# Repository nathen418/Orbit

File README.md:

# Orbit

# What happened here?
Old design files for an Arduino based clock I was building. Most stuff here is not mine, I was going to modify the files. Lost all of my work. This repo exists only so that I may return to the project at a later date. At the moment I have no energy or will to continue working on it as months of work has been lost. I got as far as fully working code and fully working hardware. I had the pcb's printed and soldered everything onto them. They worked perfectly. I still have all of the 8 revisions to the hardware. MONTHS of work gone, so 🤷‍♂️ I don't know what I am going to do. If I do return to the project, I will have to start from scratch, and will probably choose a Raspberry Pi Pico as the microcontroller, but I really have no idea.

Maybe in the future I will find a backup of the files and return to the project, however this seems unlikely.

Toodles.

## Questions?
- **Contact me on discord at nathen418#0002 or join my discord server at the link below**

## Modifications
- no issues will be resolved
- no pull requests wil be merged
- no comments on files will be answered.
- If you have a question, contact me through my discord

## Join my discord server:
https://dsc.gg/antaresnetwork

## License

- Im not a legal person so as long as I am credited in a somewhat obvious location, by my name or a link to this repository, I'm ok with it. If my name is not at the top of the file in a comment, it was not written by me and is only in this repo to serve as an example of something I was using for help. If my name does not appear on the file in a comment at the top, than it is not my code, it is class material.  If you have a problem with any of this, refer to my discord server and dm me.

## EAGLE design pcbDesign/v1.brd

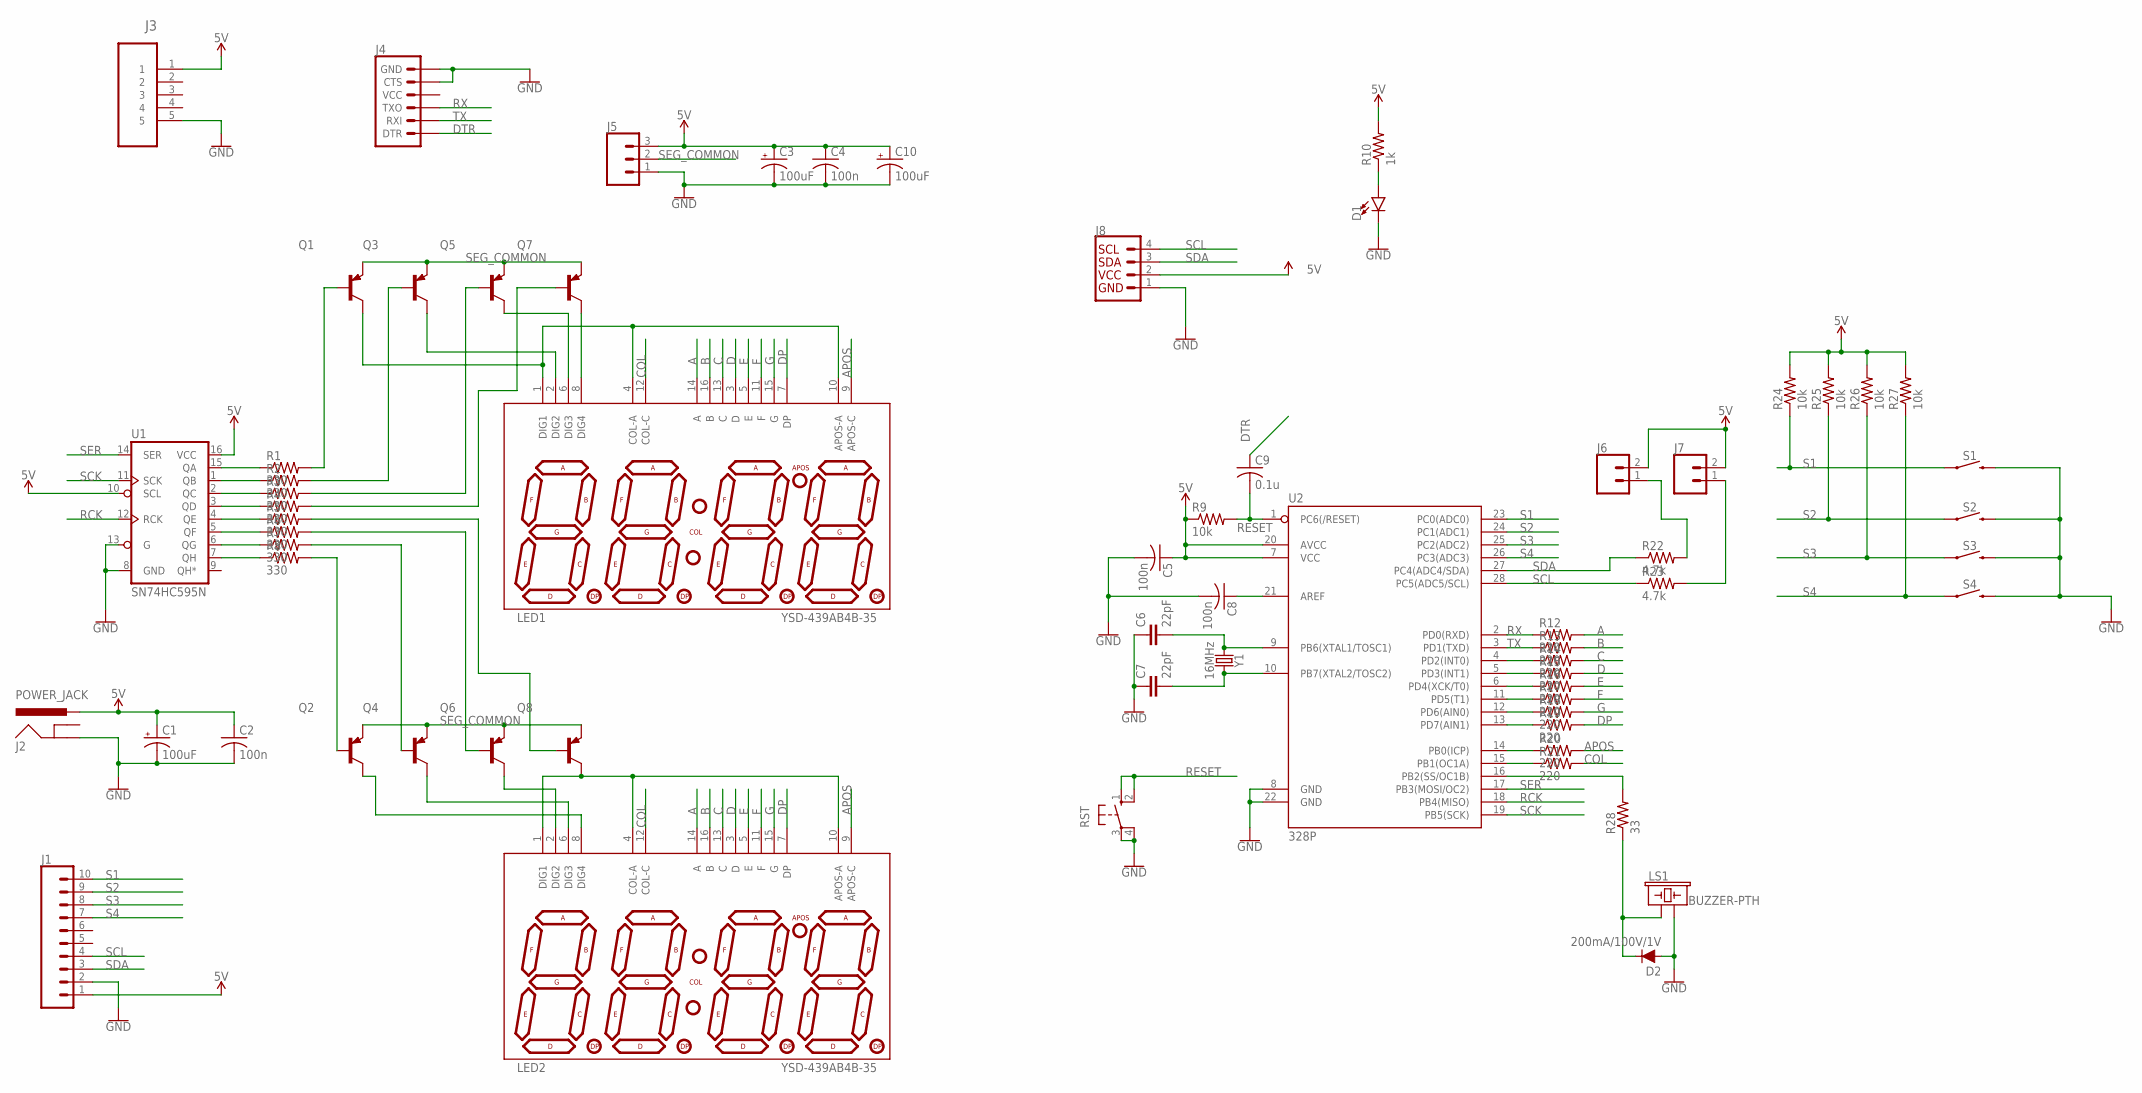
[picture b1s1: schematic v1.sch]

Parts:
C1, C3, C10: 100uF; CPOL-RADIAL-2.5MM-6.5MM
C2, C4, C5, C8: 100n; C025-025X050
C6, C7: 22pF; CAP-PTH-2.54
C9: 0.1u; C025-025X050
D1: LED3MM; LED_3MM
D2: 200mA/100V/1V; DIODE-1N4148
J1: CONN_10"; 1X10
J2: POWER_JACK; POWER_JACK_PTH
J3: 47346-0001; MOLEX_47346-0001
J4: 6_PIN_SERIAL_TARGET; 1X06
J5: CONN_03; 1X03
J6, J7: CONN_02; 1X02
J8: I2C_STANDARD; 1X04
LED1, LED2: YSD-439AB4B-35; 7-SEGMENT-4DIGIT-YOUNGSUN
LS1: BUZZER-PTH; BUZZER-12MM
Q1, Q2, Q3, Q4, Q5, Q6, Q7, Q8: 2N3906; TO92
R1, R2, R3, R4, R5, R6, R7, R8: 330; 0204/5
R9, R24, R25, R26, R27: 10k; 0204/5
R10: 1k; 0204/5
R12, R13, R14, R15, R16, R17, R18, R19, R20, R21: 220; 0204/5
R22, R23: 4.7k; 0204/5
R28: 33; 0204/5
RST: 10-XX; B3F-10XX
S1, S2, S3, S4: MOMENTARY-SWITCH-SPST-PTH-6.0MM; TACTILE_SWITCH_PTH_6.0MM
U1: SN74HC595N; DIP16
U2: 328P; DIP28
Y1: 16MHz; HC49US

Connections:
5V: C1.1 (+), C2.1, C3.1 (+), C4.1, C5.1, C10.1 (+), J1.1, J2.PWR, J3.1, J5.3, J6.2, J7.2, J8.2, R9.1, R10.2, R24.2, R25.2, R26.2, R27.2, U1.10 (SCL), U1.16 (VCC), U2.7 (VCC), U2.20 (AVCC)
A: LED1.14 (A), LED2.14 (A), R12.2
APOS: LED1.9 (APOS-C), LED2.9 (APOS-C), R20.2
B: LED1.16 (B), LED2.16 (B), R13.2
C: LED1.13 (C), LED2.13 (C), R14.2
COL: LED1.12 (COL-C), LED2.12 (COL-C), R21.2
D: LED1.3 (D), LED2.3 (D), R15.2
DP: LED1.7 (DP), LED2.7 (DP), R19.2
DTR: C9.1, J4.1 (DTR)
E: LED1.5 (E), LED2.5 (E), R16.2
F: LED1.11 (F), LED2.11 (F), R17.2
G: LED1.15 (G), LED2.15 (G), R18.2
GND: C1.2 (-), C2.2, C3.2 (-), C4.2, C5.2, C6.1, C7.1, C8.2, C10.2 (-), D1.K (C), D2.A, J1.2, J2.GND, J3.5, J4.5 (CTS), J4.6 (GND), J5.1, J8.1, LS1.- (2), RST.3, RST.4 (P1), S1.3 (2), S2.3 (2), S3.3 (2), S4.3 (2), U1.8 (GND), U1.13 (G), U2.8 (GND), U2.22 (GND)
unnamed: D1.A, R10.1
unnamed: R21.1, U2.15 (PB1(OC1A))
unnamed: R14.1, U2.4 (PD2(INT0))
unnamed: R15.1, U2.5 (PD3(INT1))
unnamed: R16.1, U2.6 (PD4(XCK/T0))
unnamed: R17.1, U2.11 (PD5(T1))
unnamed: R18.1, U2.12 (PD6(AIN0))
unnamed: R19.1, U2.13 (PD7(AIN1))
unnamed: C6.2, U2.9 (PB6(XTAL1/TOSC1)), Y1.1
unnamed: C7.2, U2.10 (PB7(XTAL2/TOSC2)), Y1.2
unnamed: LED1.1 (DIG1), LED1.4 (COL-A), LED1.10 (APOS-A), Q1.1 (C)
unnamed: LED1.6 (DIG3), Q5.1 (C)
unnamed: LED1.2 (DIG2), Q3.1 (C)
unnamed: R28.2, U2.16 (PB2(SS/OC1B))
unnamed: LED2.1 (DIG1), LED2.4 (COL-A), LED2.10 (APOS-A), Q8.1 (C)
unnamed: D2.C, LS1.+ (1), R28.1
unnamed: LED2.2 (DIG2), Q6.1 (C)
unnamed: LED2.6 (DIG3), Q4.1 (C)
unnamed: LED2.8 (DIG4), Q2.1 (C)
unnamed: LED1.8 (DIG4), Q7.1 (C)
unnamed: Q1.2 (B), R1.2
unnamed: Q3.2 (B), R2.2
unnamed: Q5.2 (B), R3.2
unnamed: Q7.2 (B), R4.2
unnamed: Q8.2 (B), R5.2
unnamed: Q6.2 (B), R6.2
unnamed: Q4.2 (B), R7.2
unnamed: Q2.2 (B), R8.2
unnamed: R1.1, U1.15 (QA)
unnamed: R2.1, U1.1 (QB)
unnamed: R3.1, U1.2 (QC)
unnamed: R4.1, U1.3 (QD)
unnamed: R5.1, U1.4 (QE)
unnamed: R6.1, U1.5 (QF)
unnamed: R7.1, U1.6 (QG)
unnamed: R8.1, U1.7 (QH)
unnamed: C8.1, U2.21 (AREF)
unnamed: J6.1, R22.2
unnamed: J7.1, R23.2
unnamed: R20.1, U2.14 (PB0(ICP))
RCK: U1.12 (RCK), U2.18 (PB4(MISO))
RESET: C9.2, R9.2, RST.1 (S), RST.2 (S1), U2.1 (PC6(/RESET))
RX: J4.3 (TXO), R12.1, U2.2 (PD0(RXD))
S1: J1.10, R24.1, S1.1, U2.23 (PC0(ADC0))
S2: J1.9, R25.1, S2.1, U2.24 (PC1(ADC1))
S3: J1.8, R26.1, S3.1, U2.25 (PC2(ADC2))
S4: J1.7, R27.1, S4.1, U2.26 (PC3(ADC3))
SCK: U1.11 (SCK), U2.19 (PB5(SCK))
SCL: J1.4, J8.4, R23.1, U2.28 (PC5(ADC5/SCL))
SDA: J1.3, J8.3, R22.1, U2.27 (PC4(ADC4/SDA))
SEG_COMMON: J5.2, Q1.3 (E), Q2.3 (E), Q3.3 (E), Q4.3 (E), Q5.3 (E), Q6.3 (E), Q7.3 (E), Q8.3 (E)
SER: U1.14 (SER), U2.17 (PB3(MOSI/OC2))
TX: J4.2 (RXI), R13.1, U2.3 (PD1(TXD))

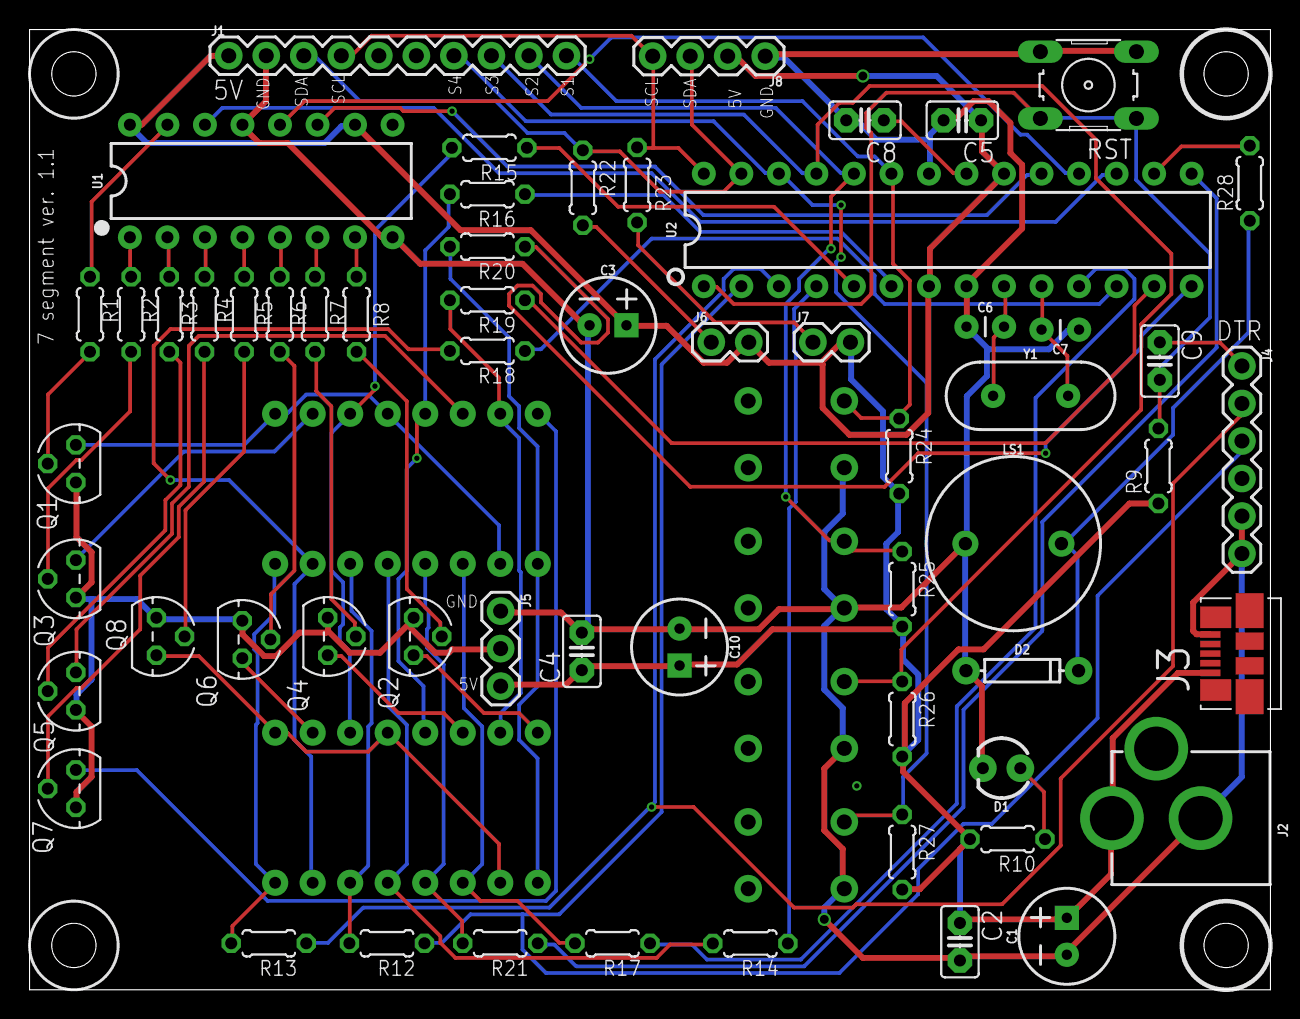
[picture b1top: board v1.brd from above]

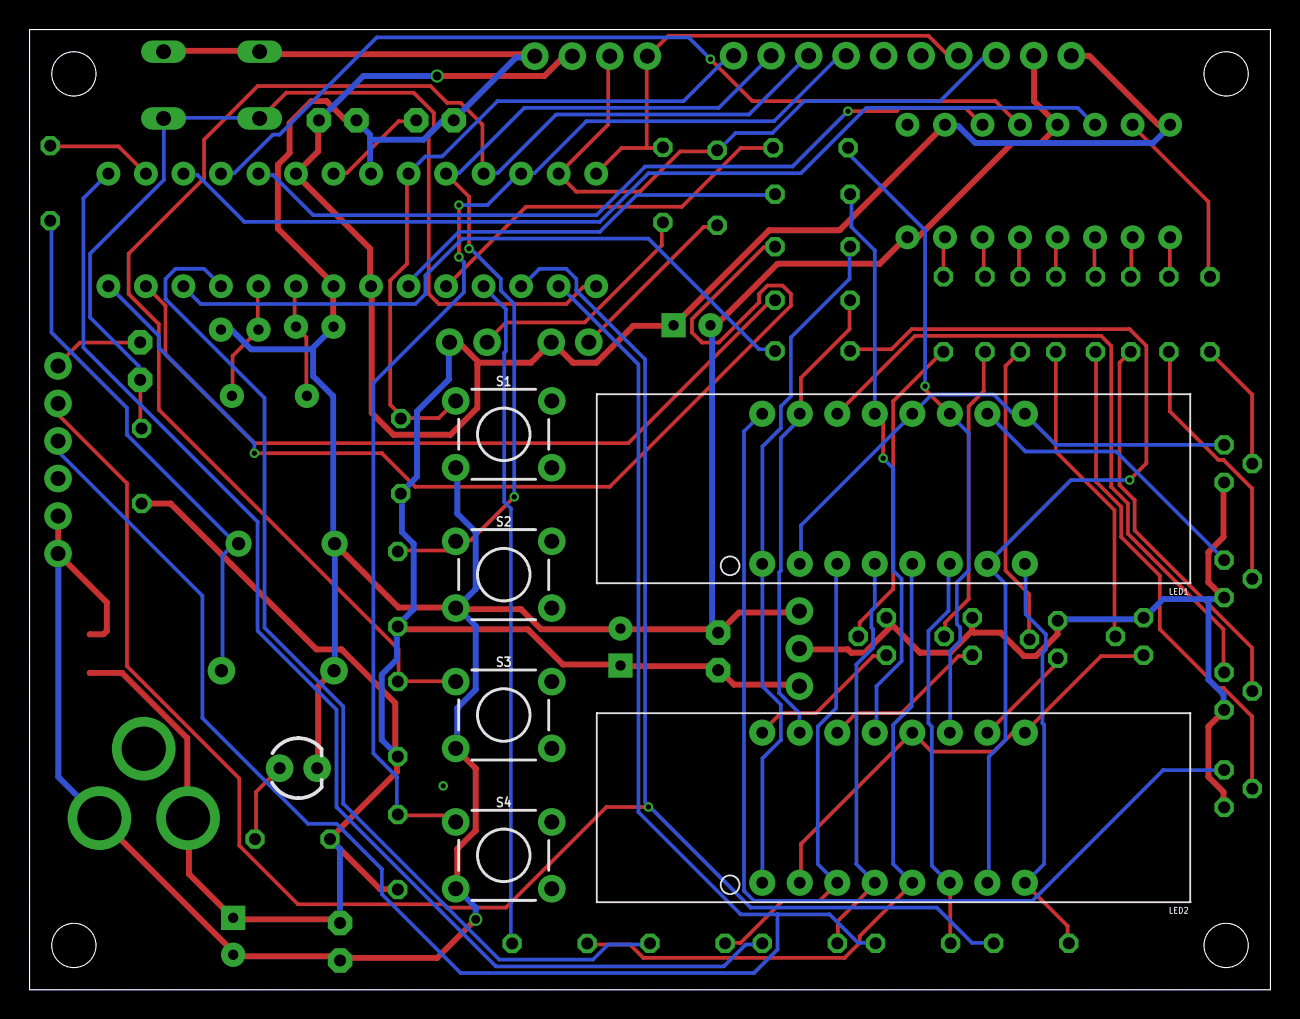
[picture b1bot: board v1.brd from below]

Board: 2 copper layers, 84.0 x 65.0 mm, 66 parts (6 on the bottom side), 66 nets.

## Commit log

2021-08-28 Rant about the lost work

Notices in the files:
parts and their libraries:
SparkFun-LED: Licensing: Creative Commons ShareAlike 4.0 International - https://creativecommons.org/licenses/by-sa/4.0
